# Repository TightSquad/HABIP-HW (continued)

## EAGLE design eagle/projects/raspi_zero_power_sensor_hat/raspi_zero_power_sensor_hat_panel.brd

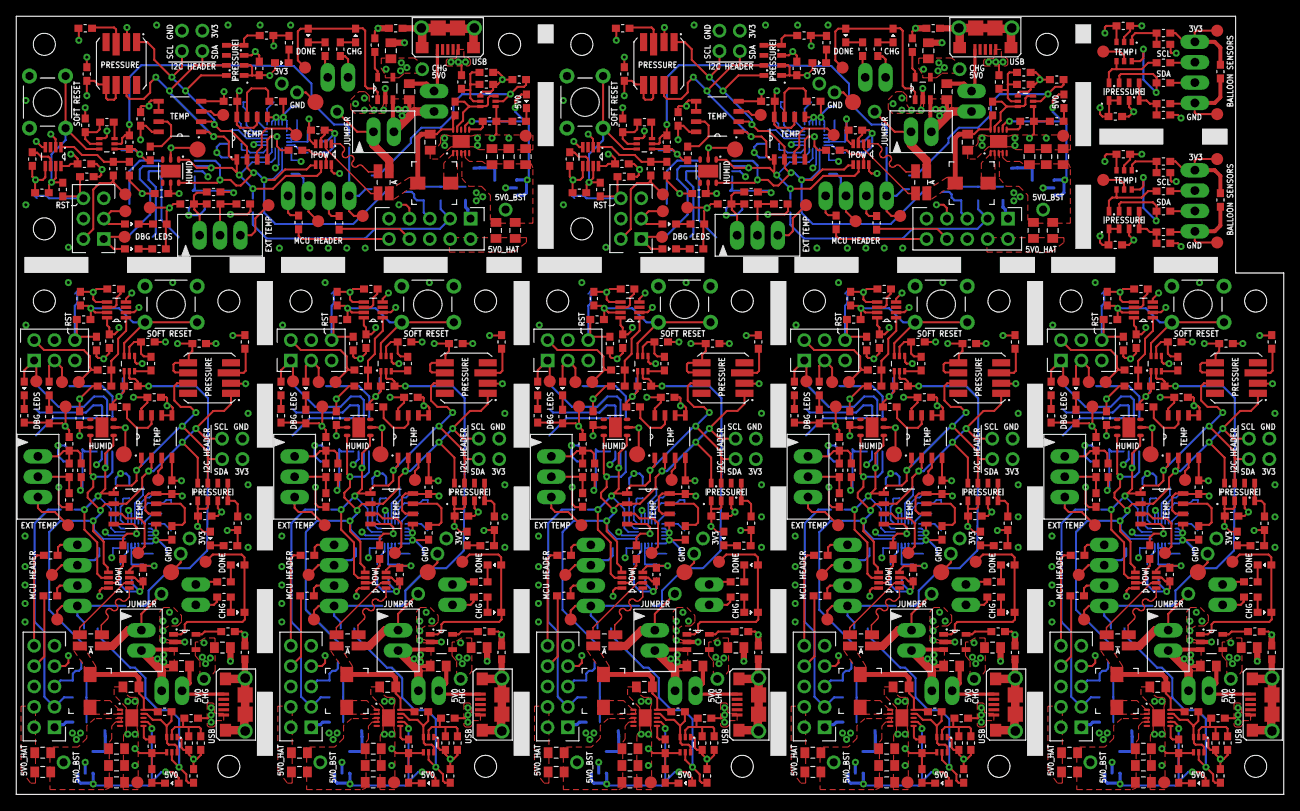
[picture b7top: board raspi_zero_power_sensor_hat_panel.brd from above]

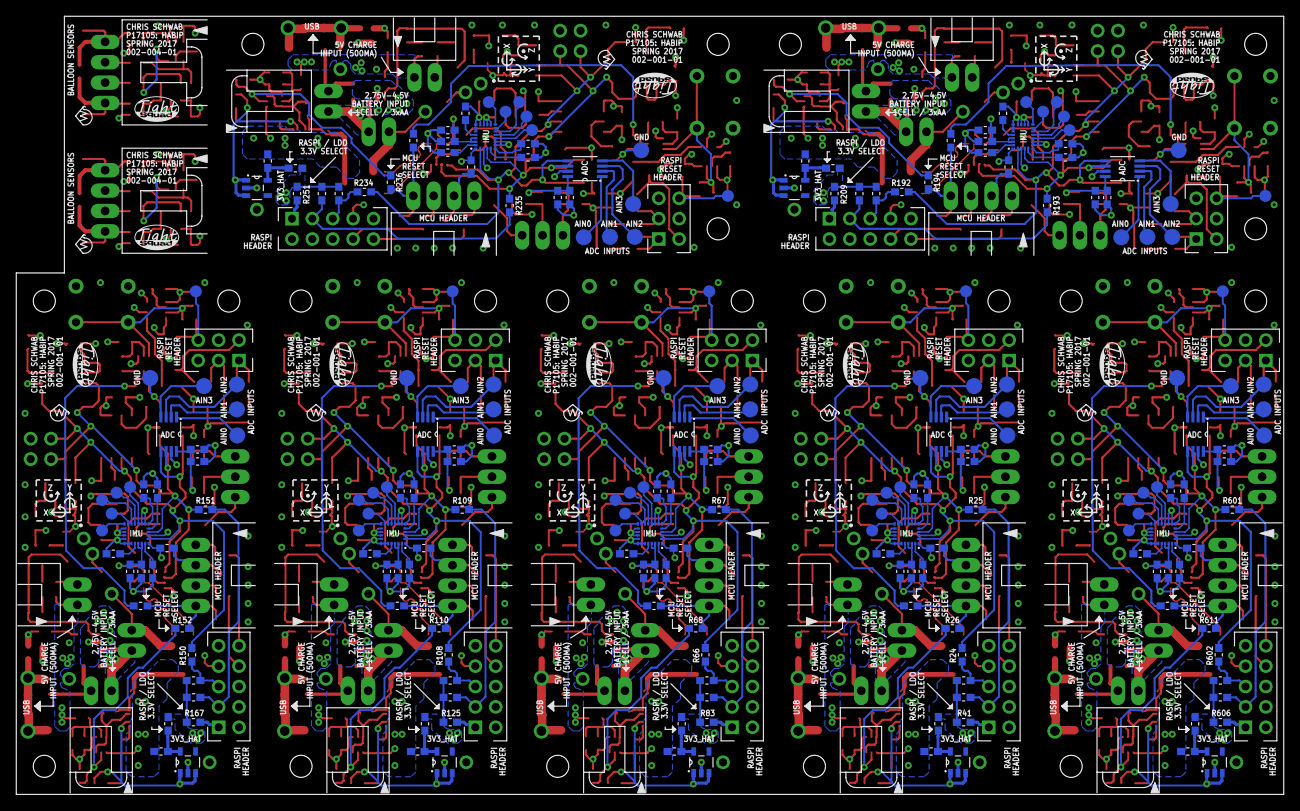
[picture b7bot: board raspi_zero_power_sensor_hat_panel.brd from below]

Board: 4 copper layers, 158.0 x 97.0 mm, 1126 parts (265 on the bottom side), 494 nets.

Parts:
BOM1, BOM4, BOM20, BOM23, BOM26, BOM42, BOM45, BOM48, BOM64, BOM67, BOM70, BOM86, BOM89, BOM92, BOM108, BOM111, BOM114, BOM130, BOM701, BOM704, BOM707: SL 70066 2PIN HOUSING; BLANK
BOM2, BOM3, BOM5, BOM6, BOM7, BOM8, BOM9, BOM10, BOM13, BOM14, BOM15, BOM21, BOM22, BOM24, BOM25, BOM27, BOM28, BOM29, BOM30, BOM31, BOM32, BOM35, BOM36, BOM37, BOM43, BOM44, BOM46, BOM47, BOM49, BOM50, BOM51, BOM52, BOM53, BOM54, BOM57, BOM58, BOM59, BOM65, BOM66, BOM68, BOM69, BOM71, BOM72, BOM73, BOM74, BOM75, BOM76, BOM79, BOM80, BOM81, BOM87, BOM88, BOM90, BOM91, BOM93, BOM94, BOM95, BOM96, BOM97, BOM98, BOM101, BOM102, BOM103, BOM109, BOM110, BOM112, BOM113, BOM115, BOM116, BOM117, BOM118, BOM119, BOM120, BOM123, BOM124, BOM125, BOM131, BOM132, BOM702, BOM703, BOM705, BOM706, BOM708, BOM709, BOM712, BOM713, BOM714, BOM715, BOM717, BOM718, BOM719: SL 70058 GOLD CRIMP; BLANK
BOM11, BOM33, BOM55, BOM77, BOM99, BOM121, BOM711: SL 70066 4PIN HOUSING; BLANK
BOM12, BOM34, BOM56, BOM78, BOM100, BOM122, BOM716: SL 70066 3PIN HOUSING; BLANK
BOM16, BOM17, BOM38, BOM39, BOM60, BOM61, BOM82, BOM83, BOM104, BOM105, BOM126, BOM127, BOM720, BOM721: 1-Wire Temperature Sensor; BLANK
BOM18, BOM40, BOM62, BOM84, BOM106, BOM128, BOM722: HEADER-RECT-MALE-2X3; BLANK
BOM19, BOM41, BOM63, BOM85, BOM107, BOM129, BOM710: HEADER-RECT-MALE-2X5; BLANK
C1, C2, C3, C4, C5, C6, C7, C8, C9, C10, C12, C14, C16, C17, C26, C27, C28, C29, C30, C31, C32, C33, C34, C35, C37, C39, C41, C42, C51, C52, C53, C54, C55, C56, C57, C58, C59, C60, C62, C64, C66, C67, C76, C77, C78, C79, C80, C81, C82, C83, C84, C85, C87, C89, C91, C92, C101, C102, C103, C104, C105, C106, C107, C108, C109, C110, C112, C114, C116, C117, C126, C127, C128, C129, C130, C131, C132, C133, C134, C135, C137, C139, C141, C142, C152, C153, C202, C203, C302, C402, C501, C502, C503, C506, C507, C508, C510, C511, C512, C513, C601, C602: 100nF; C0603
C11, C36, C61, C86, C111, C136, C509: 10uF; C0603
C13, C38, C63, C88, C113, C138, C505: 10nF; C0603
C15, C40, C65, C90, C115, C140, C404: 2.2uF; C0603
C18, C43, C68, C93, C118, C143, C504: 4.7uF; C0603
C19, C20, C22, C24, C25, C44, C45, C47, C49, C50, C69, C70, C72, C74, C75, C94, C95, C97, C99, C100, C119, C120, C122, C124, C125, C144, C145, C147, C149, C150, C301, C401, C406, C407, C408: 10uF; C0805
C21, C46, C71, C96, C121, C146, C405: 18nF; C0603
C23, C48, C73, C98, C123, C148, C403: 22uF; C0805
C151, C201: 1uF; C0603
DS1, DS7, DS13, DS19, DS25, DS31, DS401: BLUE; LED0603
DS2, DS8, DS14, DS20, DS26, DS32, DS302: GREEN; LED0603
DS3, DS4, DS5, DS6, DS9, DS10, DS11, DS12, DS15, DS16, DS17, DS18, DS21, DS22, DS23, DS24, DS27, DS28, DS29, DS30, DS33, DS34, DS35, DS36, DS301, DS402, DS601, DS602: YELLOW; LED0603
F1, F2, F3, F4, F5, F6, F601: FUSE-50MA; R0603
J1, J9, J17, J25, J33, J41, J401: MOL-SL-2-RA; MOLSL-2-RA
J2, J10, J18, J26, J34, J42, J603: MOL-SL-3-V; MOLSL-3-V
J3, J11, J19, J27, J35, J43, J604: RECEPTACLE-2x3-2.54MM; RECEPTACLE-2X3-254MM
J4, J12, J20, J28, J36, J44, J302: USB_MICROB_RECPT; MICROUSB-RIGHT
J5, J13, J21, J29, J37, J45, J301: MOL-SL-2-RA; MOLSL-2-RA_HALF
J6, J14, J22, J30, J38, J46, J601: RECEPTACLE-2x5-2.54MM; RECEPTACLE-2X5-254MM
J7, J15, J23, J31, J39, J47, J402: MOL-SL-2-V; MOLSL-2-V
J8, J16, J24, J32, J40, J48, J602: MOL-SL-4-RA; MOLSL-4-RA_HALF
J49, J201: MOL-SL-4-RA; MOLSL-4-RA
L1, L2, L3, L4, L5, L6, L401: 1.0uH; SMD410P190X160-2N
LOGO1, LOGO3, LOGO5, LOGO7, LOGO9, LOGO11, LOGO13, LOGO201, LOGO602: SQUAD_LOGO
LOGO2, LOGO4, LOGO6, LOGO8, LOGO10, LOGO12, LOGO14, LOGO202, LOGO601: CMS_LOGO
OUTLINE1, OUTLINE2, OUTLINE3, OUTLINE4, OUTLINE5, OUTLINE6, OUTLINE601: RASPI_ZERO_OUTLINE_3S0C_ONLY; RASPI_ZERO_3STANDOFFS_ONLY
Q1, Q2, Q3, Q4, Q5, Q6, Q7, Q8, Q9, Q10, Q11, Q12, Q301, Q401: SSM6N7002KFU; SOT363P080X040-6N
R1, R2, R3, R10, R11, R17, R19, R20, R23, R24, R25, R26, R27, R32, R33, R34, R35, R37, R38, R40, R41, R43, R44, R45, R52, R53, R59, R61, R62, R65, R66, R67, R68, R69, R74, R75, R76, R77, R79, R80, R82, R83, R85, R86, R87, R94, R95, R101, R103, R104, R107, R108, R109, R110, R111, R116, R117, R118, R119, R121, R122, R124, R125, R127, R128, R129, R136, R137, R143, R145, R146, R149, R150, R151, R152, R153, R158, R159, R160, R161, R163, R164, R166, R167, R169, R170, R171, R178, R179, R185, R187, R188, R191, R192, R193, R194, R195, R200, R201, R202, R203, R205, R206, R208, R209, R211, R212, R213, R220, R221, R227, R229, R230, R233, R234, R235, R236, R237, R242, R243, R244, R245, R247, R248, R250, R251, R253, R254, R255, R256, R257, R258, R259, R260, R261, R262, R263, R264, R301, R305, R306, R307, R308, R401, R501, R502, R503, R504, R505, R506, R507, R601, R602, R605, R606, R609, R610, R611, R612: 0.0; R0603
R4, R5, R6, R8, R9, R12, R13, R14, R18, R46, R47, R48, R50, R51, R54, R55, R56, R60, R88, R89, R90, R92, R93, R96, R97, R98, R102, R130, R131, R132, R134, R135, R138, R139, R140, R144, R172, R173, R174, R176, R177, R180, R181, R182, R186, R214, R215, R216, R218, R219, R222, R223, R224, R228, R302, R303, R304, R407, R410, R603, R604, R607, R608: 2k; R0603
R7, R49, R91, R133, R175, R217, R613: 4.7k; R0603
R15, R16, R28, R29, R30, R31, R57, R58, R70, R71, R72, R73, R99, R100, R112, R113, R114, R115, R141, R142, R154, R155, R156, R157, R183, R184, R196, R197, R198, R199, R225, R226, R238, R239, R240, R241, R309, R310, R311, R404, R405, R406: 10k; R0603
R21, R42, R63, R84, R105, R126, R147, R168, R189, R210, R231, R252, R408, R409: 0.0; R0805
R22, R36, R64, R78, R106, R120, R148, R162, R190, R204, R232, R246, R312, R403: 49.9; R0603
R39, R81, R123, R165, R207, R249, R402: 0.033; RS1206
S1, S2, S3, S4, S5, S6, S301: PB; TACTILE-PTH
TP1, TP2, TP3, TP4, TP5, TP6, TP7, TP8, TP9, TP10, TP11, TP12, TP13, TP21, TP24, TP26, TP27, TP34, TP35, TP36, TP37, TP38, TP39, TP40, TP41, TP42, TP43, TP44, TP45, TP46, TP54, TP57, TP59, TP60, TP67, TP68, TP69, TP70, TP71, TP72, TP73, TP74, TP75, TP76, TP77, TP78, TP79, TP87, TP90, TP92, TP93, TP100, TP101, TP102, TP103, TP104, TP105, TP106, TP107, TP108, TP109, TP110, TP111, TP112, TP120, TP123, TP125, TP126, TP133, TP134, TP135, TP136, TP137, TP138, TP139, TP140, TP141, TP142, TP143, TP144, TP145, TP153, TP156, TP158, TP159, TP166, TP167, TP168, TP169, TP170, TP171, TP172, TP173, TP174, TP175, TP176, TP177, TP178, TP186, TP189, TP191, TP192, TP199, TP200, TP201, TP202, TP203, TP204, TP304, TP404, TP506, TP507, TP508, TP509, TP510, TP511, TP512, TP605, TP606, TP607, TP608, TP609, TP610, TP611, TP612: TP15R
TP14, TP15, TP16, TP17, TP18, TP32, TP33, TP47, TP48, TP49, TP50, TP51, TP65, TP66, TP80, TP81, TP82, TP83, TP84, TP98, TP99, TP113, TP114, TP115, TP116, TP117, TP131, TP132, TP146, TP147, TP148, TP149, TP150, TP164, TP165, TP179, TP180, TP181, TP182, TP183, TP197, TP198, TP303, TP501, TP502, TP503, TP504, TP505, TP513: TP20R
TP19, TP20, TP22, TP23, TP25, TP28, TP29, TP30, TP31, TP52, TP53, TP55, TP56, TP58, TP61, TP62, TP63, TP64, TP85, TP86, TP88, TP89, TP91, TP94, TP95, TP96, TP97, TP118, TP119, TP121, TP122, TP124, TP127, TP128, TP129, TP130, TP151, TP152, TP154, TP155, TP157, TP160, TP161, TP162, TP163, TP184, TP185, TP187, TP188, TP190, TP193, TP194, TP195, TP196, TP301, TP302, TP401, TP402, TP403, TP601, TP602, TP603, TP604: TP_TH102
U1, U13, U25, U37, U49, U61, U504: INA219AIDCNR; SOT65P110X045-8N
U2, U14, U26, U38, U50, U62, U73, U202, U506: MS560702BA03-50; SMD125P110X060-8N
U3, U15, U27, U39, U51, U63, U503: MAX11613EUA+; SOP65P135X040-8N
U4, U16, U28, U40, U52, U64, U507: MS580305BA01; SMD125130P225X090-8N
U5, U17, U29, U41, U53, U65, U401: TLV71333P; SOT23P105X060-5N
U6, U18, U30, U42, U54, U66, U302: MAX6371; SOT23P130X045-8N
U7, U19, U31, U43, U55, U67, U505: LSM9DS1TR; LGA043P045X033-24N
U8, U20, U32, U44, U56, U68, U508: SI7021; DFN-100P085X045-T-6N
U9, U21, U33, U45, U57, U69, U301: MCP73831T-2AC; SOT23P110X060-5N
U10, U22, U34, U46, U58, U70, U402: TPS61232; DRC0010G_SM
U11, U12, U23, U24, U35, U36, U47, U48, U59, U60, U71, U72, U501, U502: PCT2075D,118; SOIC127P130X0600-8N
U74, U201: PCT2075GVJ; TSOP95P080X055-6N

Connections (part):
3V3_HAT_PG: DS402.1, R410.2
3V3_HAT_PG1: DS4.1, R18.2
3V3_HAT_PG2: DS10.1, R60.2
3V3_HAT_PG3: DS16.1, R102.2
3V3_HAT_PG4: DS22.1, R144.2
3V3_HAT_PG5: DS28.1, R186.2
3V3_HAT_PG6: DS34.1, R228.2
5V0_BST_PG: DS401.1, R407.2
5V0_BST_PG1: DS1.1, R4.2
5V0_BST_PG2: DS7.1, R46.2
5V0_BST_PG3: DS13.1, R88.2
5V0_BST_PG4: DS19.1, R130.2
5V0_BST_PG5: DS25.1, R172.2
5V0_BST_PG6: DS31.1, R214.2
ADC_AIN0: TP504.TP, U503.1
ADC_AIN1: TP503.TP, U503.2
ADC_AIN2: TP502.TP, U503.3
ADC_AIN3: TP15.TP, U3.3
ADC_AIN3_REF: TP501.TP, U503.4
ADC_AIN3_REF1: TP14.TP, U3.4
ADC_AIN3_REF2: TP47.TP, U15.4
ADC_AIN3_REF3: TP80.TP, U27.4
ADC_AIN3_REF4: TP113.TP, U39.4
ADC_AIN3_REF5: TP146.TP, U51.4
ADC_AIN3_REF6: TP179.TP, U63.4
ADC_AIN4: TP16.TP, U3.2
ADC_AIN5: TP17.TP, U3.1
ADC_AIN6: TP48.TP, U15.3
ADC_AIN7: TP49.TP, U15.2
ADC_AIN8: TP50.TP, U15.1
ADC_AIN9: TP81.TP, U27.3
ADC_AIN10: TP82.TP, U27.2
ADC_AIN11: TP83.TP, U27.1
ADC_AIN12: TP114.TP, U39.3
ADC_AIN13: TP115.TP, U39.2
ADC_AIN14: TP116.TP, U39.1
ADC_AIN15: TP147.TP, U51.3
ADC_AIN16: TP148.TP, U51.2
ADC_AIN17: TP149.TP, U51.1
ADC_AIN18: TP180.TP, U63.3
ADC_AIN19: TP181.TP, U63.2
ADC_AIN20: TP182.TP, U63.1
BST_EN: Q401.3, Q401.6, R405.1, U402.9
BST_EN1: Q1.3, Q1.6, R29.1, U10.9
BST_EN2: Q3.3, Q3.6, R71.1, U22.9
BST_EN3: Q5.3, Q5.6, R113.1, U34.9
BST_EN4: Q7.3, Q7.6, R155.1, U46.9
BST_EN5: Q9.3, Q9.6, R197.1, U58.9
BST_EN6: Q11.3, Q11.6, R239.1, U70.9
BST_SS: C405.1, U402.6
BST_SS1: C21.1, U10.6
BST_SS2: C46.1, U22.6
BST_SS3: C71.1, U34.6
BST_SS4: C96.1, U46.6
BST_SS5: C121.1, U58.6
BST_SS6: C146.1, U70.6
BST_SW: L401.2, U402.1, U402.2
BST_SW1: L1.2, U10.1, U10.2
BST_SW2: L2.2, U22.1, U22.2
BST_SW3: L3.2, U34.1, U34.2
BST_SW4: L4.2, U46.1, U46.2
BST_SW5: L5.2, U58.1, U58.2
BST_SW6: L6.2, U70.1, U70.2
CHG_DISABLE_GATE: C404.1, Q401.2, R403.2, R404.2
CHG_DISABLE_GATE1: C15.1, Q1.2, R30.2, R36.2
CHG_DISABLE_GATE2: C40.1, Q3.2, R72.2, R78.2
CHG_DISABLE_GATE3: C65.1, Q5.2, R114.2, R120.2
CHG_DISABLE_GATE4: C90.1, Q7.2, R156.2, R162.2
CHG_DISABLE_GATE5: C115.1, Q9.2, R198.2, R204.2
CHG_DISABLE_GATE6: C140.1, Q11.2, R240.2, R246.2
CHG_DONE: DS302.1, R304.2
CHG_DONE1: DS2.1, R14.2
CHG_DONE2: DS8.1, R56.2
CHG_DONE3: DS14.1, R98.2
CHG_DONE4: DS20.1, R140.2
CHG_DONE5: DS26.1, R182.2
CHG_DONE6: DS32.1, R224.2
CHG_ON: DS301.2, R303.1
CHG_ON1: DS3.2, R13.1
CHG_ON2: DS9.2, R55.1
CHG_ON3: DS15.2, R97.1
CHG_ON4: DS21.2, R139.1
CHG_ON5: DS27.2, R181.1
CHG_ON6: DS33.2, R223.1
CHG_PROG: R302.2, U301.5
CHG_PROG1: R12.2, U9.5
CHG_PROG2: R54.2, U21.5
CHG_PROG3: R96.2, U33.5
CHG_PROG4: R138.2, U45.5
CHG_PROG5: R180.2, U57.5
CHG_PROG6: R222.2, U69.5
CHG_STAT: DS301.1, DS302.2, TP304.TP, U301.1
CHG_STAT1: DS2.2, DS3.1, TP21.TP, U9.1
CHG_STAT2: DS8.2, DS9.1, TP54.TP, U21.1
CHG_STAT3: DS14.2, DS15.1, TP87.TP, U33.1
CHG_STAT4: DS20.2, DS21.1, TP120.TP, U45.1
CHG_STAT5: DS26.2, DS27.1, TP153.TP, U57.1
CHG_STAT6: DS32.2, DS33.1, TP186.TP, U69.1
DBG_LED0: DS601.1, R607.2
DBG_LED1: DS602.1, R608.2
DBG_LED2: DS6.1, R9.2
DBG_LED3: DS5.1, R8.2
DBG_LED4: DS12.1, R51.2
DBG_LED5: DS11.1, R50.2
DBG_LED6: DS18.1, R93.2
DBG_LED7: DS17.1, R92.2
DBG_LED8: DS24.1, R135.2
DBG_LED9: DS23.1, R134.2
DBG_LED10: DS30.1, R177.2
DBG_LED11: DS29.1, R176.2
DBG_LED12: DS36.1, R219.2
DBG_LED13: DS35.1, R218.2
FET_D: Q301.3, R305.2
FET_D1: Q2.3, R37.2
FET_D2: Q4.3, R79.2
FET_D3: Q6.3, R121.2
FET_D4: Q8.3, R163.2
FET_D5: Q10.3, R205.2
FET_D6: Q12.3, R247.2
FET_G: Q301.5, R305.1, R306.1
FET_G1: Q2.5, R37.1, R38.1
FET_G2: Q4.5, R79.1, R80.1
FET_G3: Q6.5, R121.1, R122.1
FET_G4: Q8.5, R163.1, R164.1
FET_G5: Q10.5, R205.1, R206.1
FET_G6: Q12.5, R247.1, R248.1
GND: C301.2, C302.2, C401.2, C402.2, C403.2, C404.2, C405.2, C406.2, C407.2, C408.2, C501.1, C502.1, C503.2, C504.2, C505.2, C506.1, C507.2, C508.2, C509.2, C510.2, C511.1, C512.1, C513.1, C601.2, C602.2, J301.2, J302.5, J401.2, J601.6, J601.9, J602.2, J603.3, J604.4, J604.5, Q301.1, Q301.4, Q401.1, Q401.4, R301.1, R302.1, R304.1, R306.2, R309.1, R310.1, R404.1, R406.1, R407.1, R410.1, R501.1, R502.1, R503.1, R504.1, R505.1, R507.1, R607.1, R608.1, S301.1, S301.2, TP302.1, TP303.TP, TP404.TP, TP505.TP, TP513.TP, TP604.1, TP608.TP, TP610.TP, TP612.TP, U301.2, U302.2, U401.2, U402.11, U501.4, U501.5, U501.6, U502.4, U502.5, U503.7, U504.3, U505.14, U505.15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
GND1: C1.1, C2.1, C3.1, C4.1, C5.2, C6.2, C7.1, C8.1, C9.2, C10.2, C11.2, C12.2, C13.2, C14.2, C15.2, C16.2, C17.2, C18.2, C19.2, C20.2, C21.2, C22.2, C23.2, C24.2, C25.2, J1.2, J2.3, J3.4, J3.5, J4.5, J5.2, J6.6, J6.9, J8.2, Q1.1, Q1.4, Q2.1, Q2.4, R1.1, R2.1, R3.1, R4.1, R8.1, R9.1, R10.1, R12.1, R14.1, R16.1, R18.1, R19.1, R20.1, R23.1, R28.1, R30.1, R31.1, R38.2, S1.1, S1.2, TP11.TP, TP12.TP, TP13.TP, TP18.TP, TP20.1, TP24.TP, TP31.1, TP32.TP, TP33.TP, U1.3, U2.3, U3.7, U4.2, U5.2, U6.2, U7.14, U7.15, U7.16, U7.17, U7.18, U7.19, U7.20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
GND2: C26.1, C27.1, C28.1, C29.1, C30.2, C31.2, C32.1, C33.1, C34.2, C35.2, C36.2, C37.2, C38.2, C39.2, C40.2, C41.2, C42.2, C43.2, C44.2, C45.2, C46.2, C47.2, C48.2, C49.2, C50.2, J9.2, J10.3, J11.4, J11.5, J12.5, J13.2, J14.6, J14.9, J16.2, Q3.1, Q3.4, Q4.1, Q4.4, R43.1, R44.1, R45.1, R46.1, R50.1, R51.1, R52.1, R54.1, R56.1, R58.1, R60.1, R61.1, R62.1, R65.1, R70.1, R72.1, R73.1, R80.2, S2.1, S2.2, TP44.TP, TP45.TP, TP46.TP, TP51.TP, TP53.1, TP57.TP, TP64.1, TP65.TP, TP66.TP, U13.3, U14.3, U15.7, U16.2, U17.2, U18.2, U19.14, U19.15, U19.16, U19.17, U19.18, U19.19, U19.20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
GND3: C51.1, C52.1, C53.1, C54.1, C55.2, C56.2, C57.1, C58.1, C59.2, C60.2, C61.2, C62.2, C63.2, C64.2, C65.2, C66.2, C67.2, C68.2, C69.2, C70.2, C71.2, C72.2, C73.2, C74.2, C75.2, J17.2, J18.3, J19.4, J19.5, J20.5, J21.2, J22.6, J22.9, J24.2, Q5.1, Q5.4, Q6.1, Q6.4, R85.1, R86.1, R87.1, R88.1, R92.1, R93.1, R94.1, R96.1, R98.1, R100.1, R102.1, R103.1, R104.1, R107.1, R112.1, R114.1, R115.1, R122.2, S3.1, S3.2, TP77.TP, TP78.TP, TP79.TP, TP84.TP, TP86.1, TP90.TP, TP97.1, TP98.TP, TP99.TP, U25.3, U26.3, U27.7, U28.2, U29.2, U30.2, U31.14, U31.15, U31.16, U31.17, U31.18, U31.19, U31.20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
GND4: C76.1, C77.1, C78.1, C79.1, C80.2, C81.2, C82.1, C83.1, C84.2, C85.2, C86.2, C87.2, C88.2, C89.2, C90.2, C91.2, C92.2, C93.2, C94.2, C95.2, C96.2, C97.2, C98.2, C99.2, C100.2, J25.2, J26.3, J27.4, J27.5, J28.5, J29.2, J30.6, J30.9, J32.2, Q7.1, Q7.4, Q8.1, Q8.4, R127.1, R128.1, R129.1, R130.1, R134.1, R135.1, R136.1, R138.1, R140.1, R142.1, R144.1, R145.1, R146.1, R149.1, R154.1, R156.1, R157.1, R164.2, S4.1, S4.2, TP110.TP, TP111.TP, TP112.TP, TP117.TP, TP119.1, TP123.TP, TP130.1, TP131.TP, TP132.TP, U37.3, U38.3, U39.7, U40.2, U41.2, U42.2, U43.14, U43.15, U43.16, U43.17, U43.18, U43.19, U43.20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
GND5: C101.1, C102.1, C103.1, C104.1, C105.2, C106.2, C107.1, C108.1, C109.2, C110.2, C111.2, C112.2, C113.2, C114.2, C115.2, C116.2, C117.2, C118.2, C119.2, C120.2, C121.2, C122.2, C123.2, C124.2, C125.2, J33.2, J34.3, J35.4, J35.5, J36.5, J37.2, J38.6, J38.9, J40.2, Q9.1, Q9.4, Q10.1, Q10.4, R169.1, R170.1, R171.1, R172.1, R176.1, R177.1, R178.1, R180.1, R182.1, R184.1, R186.1, R187.1, R188.1, R191.1, R196.1, R198.1, R199.1, R206.2, S5.1, S5.2, TP143.TP, TP144.TP, TP145.TP, TP150.TP, TP152.1, TP156.TP, TP163.1, TP164.TP, TP165.TP, U49.3, U50.3, U51.7, U52.2, U53.2, U54.2, U55.14, U55.15, U55.16, U55.17, U55.18, U55.19, U55.20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
GND6: C126.1, C127.1, C128.1, C129.1, C130.2, C131.2, C132.1, C133.1, C134.2, C135.2, C136.2, C137.2, C138.2, C139.2, C140.2, C141.2, C142.2, C143.2, C144.2, C145.2, C146.2, C147.2, C148.2, C149.2, C150.2, J41.2, J42.3, J43.4, J43.5, J44.5, J45.2, J46.6, J46.9, J48.2, Q11.1, Q11.4, Q12.1, Q12.4, R211.1, R212.1, R213.1, R214.1, R218.1, R219.1, R220.1, R222.1, R224.1, R226.1, R228.1, R229.1, R230.1, R233.1, R238.1, R240.1, R241.1, R248.2, S6.1, S6.2, TP176.TP, TP177.TP, TP178.TP, TP183.TP, TP185.1, TP189.TP, TP196.1, TP197.TP, TP198.TP, U61.3, U62.3, U63.7, U64.2, U65.2, U66.2, U67.14, U67.15, U67.16, U67.17, U67.18, U67.19, U67.20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
GND7: C201.2, C202.1, C203.1, J201.4, R255.1, R256.1, TP202.TP, U201.2, U202.3
GND8: C151.2, C152.1, C153.1, J49.4, R261.1, R262.1, TP200.TP, U73.3, U74.2
I2C1_RASPI_SCL: R602.1, TP603.1, U501.2, U502.2, U503.5, U504.5, U505.2, U506.8, U507.1, U508.6
I2C1_RASPI_SCL1: R24.1, TP30.1, U1.5, U2.8, U3.5, U4.1, U7.2, U8.6, U11.2, U12.2
I2C1_RASPI_SCL2: R66.1, TP63.1, U13.5, U14.8, U15.5, U16.1, U19.2, U20.6, U23.2, U24.2
I2C1_RASPI_SCL3: R108.1, TP96.1, U25.5, U26.8, U27.5, U28.1, U31.2, U32.6, U35.2, U36.2
I2C1_RASPI_SCL4: R150.1, TP129.1, U37.5, U38.8, U39.5, U40.1, U43.2, U44.6, U47.2, U48.2
I2C1_RASPI_SCL5: R192.1, TP162.1, U49.5, U50.8, U51.5, U52.1, U55.2, U56.6, U59.2, U60.2
I2C1_RASPI_SCL6: R234.1, TP195.1, U61.5, U62.8, U63.5, U64.1, U67.2, U68.6, U71.2, U72.2
I2C1_RASPI_SCL_R: J601.5, R602.2, R604.1
I2C1_RASPI_SCL_R1: J6.5, R6.1, R24.2
I2C1_RASPI_SCL_R2: J14.5, R48.1, R66.2
I2C1_RASPI_SCL_R3: J22.5, R90.1, R108.2
I2C1_RASPI_SCL_R4: J30.5, R132.1, R150.2
I2C1_RASPI_SCL_R5: J38.5, R174.1, R192.2
I2C1_RASPI_SCL_R6: J46.5, R216.1, R234.2
I2C1_RASPI_SDA: R601.1, TP602.1, U501.1, U502.1, U503.6, U504.6, U505.4, U506.7, U507.7, U508.1
I2C1_RASPI_SDA1: R25.1, TP29.1, U1.6, U2.7, U3.6, U4.7, U7.4, U8.1, U11.1, U12.1
I2C1_RASPI_SDA2: R67.1, TP62.1, U13.6, U14.7, U15.6, U16.7, U19.4, U20.1, U23.1, U24.1
I2C1_RASPI_SDA3: R109.1, TP95.1, U25.6, U26.7, U27.6, U28.7, U31.4, U32.1, U35.1, U36.1
I2C1_RASPI_SDA4: R151.1, TP128.1, U37.6, U38.7, U39.6, U40.7, U43.4, U44.1, U47.1, U48.1
I2C1_RASPI_SDA5: R193.1, TP161.1, U49.6, U50.7, U51.6, U52.7, U55.4, U56.1, U59.1, U60.1
I2C1_RASPI_SDA6: R235.1, TP194.1, U61.6, U62.7, U63.6, U64.7, U67.4, U68.1, U71.1, U72.1
I2C1_RASPI_SDA_R: J601.3, R601.2, R603.1
I2C1_RASPI_SDA_R1: J6.3, R5.1, R25.2
I2C1_RASPI_SDA_R2: J14.3, R47.1, R67.2
I2C1_RASPI_SDA_R3: J22.3, R89.1, R109.2
I2C1_RASPI_SDA_R4: J30.3, R131.1, R151.2
I2C1_RASPI_SDA_R5: J38.3, R173.1, R193.2
I2C1_RASPI_SDA_R6: J46.3, R215.1, R235.2
I2C_SCL: R253.2, U201.4, U202.8
I2C_SCL1: R259.2, U73.8, U74.4
I2C_SCL_CONN: J201.2, R253.1
I2C_SCL_CONN1: J49.2, R259.1
I2C_SDA: R254.2, U201.6, U202.7
I2C_SDA1: R260.2, U73.7, U74.6
I2C_SDA_COMM: J201.3, R254.1
I2C_SDA_COMM1: J49.3, R260.1
IMON_A0: R504.2, U504.7
IMON_A1: R3.2, U1.7
IMON_A2: R45.2, U13.7
IMON_A3: R87.2, U25.7
IMON_A4: R129.2, U37.7
IMON_A5: R171.2, U49.7
IMON_A6: R213.2, U61.7
IMU_C1: C508.1, U505.24
IMU_C2: C12.1, U7.24
IMU_C3: C37.1, U19.24
IMU_C4: C62.1, U31.24
IMU_C5: C87.1, U43.24
IMU_C6: C112.1, U55.24
IMU_C7: C137.1, U67.24
IMU_CAP: C505.1, U505.21
IMU_CAP1: C13.1, U7.21
IMU_CAP2: C38.1, U19.21
IMU_CAP3: C63.1, U31.21
IMU_CAP4: C88.1, U43.21
IMU_CAP5: C113.1, U55.21
IMU_CAP6: C138.1, U67.21
IMU_DEN_AG: TP512.TP, U505.13
IMU_DEN_AG1: TP10.TP, U7.13
IMU_DEN_AG2: TP43.TP, U19.13
IMU_DEN_AG3: TP76.TP, U31.13
IMU_DEN_AG4: TP109.TP, U43.13
IMU_DEN_AG5: TP142.TP, U55.13
IMU_DEN_AG6: TP175.TP, U67.13
IMU_DRDY_M: TP508.TP, U505.9
IMU_DRDY_M1: TP6.TP, U7.9
IMU_DRDY_M2: TP39.TP, U19.9
IMU_DRDY_M3: TP72.TP, U31.9
IMU_DRDY_M4: TP105.TP, U43.9
IMU_DRDY_M5: TP138.TP, U55.9
IMU_DRDY_M6: TP171.TP, U67.9
IMU_INT1_AG: TP510.TP, U505.11
IMU_INT1_AG1: TP8.TP, U7.11
IMU_INT1_AG2: TP41.TP, U19.11
IMU_INT1_AG3: TP74.TP, U31.11
IMU_INT1_AG4: TP107.TP, U43.11
IMU_INT1_AG5: TP140.TP, U55.11
IMU_INT1_AG6: TP173.TP, U67.11
IMU_INT2_AG: TP511.TP, U505.12
IMU_INT2_AG1: TP9.TP, U7.12
IMU_INT2_AG2: TP42.TP, U19.12
IMU_INT2_AG3: TP75.TP, U31.12
IMU_INT2_AG4: TP108.TP, U43.12
IMU_INT2_AG5: TP141.TP, U55.12
IMU_INT2_AG6: TP174.TP, U67.12
IMU_INT_M: TP509.TP, U505.10
IMU_INT_M1: TP7.TP, U7.10
IMU_INT_M2: TP40.TP, U19.10
IMU_INT_M3: TP73.TP, U31.10
IMU_INT_M4: TP106.TP, U43.10
IMU_INT_M5: TP139.TP, U55.10
IMU_INT_M6: TP172.TP, U67.10
IMU_SDO_AG: R505.2, U505.5
IMU_SDO_AG1: R19.2, U7.5
IMU_SDO_AG2: R61.2, U19.5
IMU_SDO_AG3: R103.2, U31.5
IMU_SDO_AG4: R145.2, U43.5
IMU_SDO_AG5: R187.2, U55.5
IMU_SDO_AG6: R229.2, U67.5
IMU_SDO_M: R503.2, U505.6
IMU_SDO_M1: R20.2, U7.6
IMU_SDO_M2: R62.2, U19.6
IMU_SDO_M3: R104.2, U31.6
IMU_SDO_M4: R146.2, U43.6
IMU_SDO_M5: R188.2, U55.6
IMU_SDO_M6: R230.2, U67.6
MCU_TO_BST_RESET: Q401.5, R406.2, R611.2
MCU_TO_BST_RESET1: Q1.5, R26.2, R31.2
MCU_TO_BST_RESET2: Q3.5, R68.2, R73.2
MCU_TO_BST_RESET3: Q5.5, R110.2, R115.2
MCU_TO_BST_RESET4: Q7.5, R152.2, R157.2
MCU_TO_BST_RESET5: Q9.5, R194.2, R199.2
MCU_TO_BST_RESET6: Q11.5, R236.2, R241.2
MCU_TO_HAT_RESET: J602.4, R611.1, R612.1, TP607.TP
MCU_TO_HAT_RESET1: J8.4, R26.1, R27.1, TP5.TP
MCU_TO_HAT_RESET2: J16.4, R68.1, R69.1, TP38.TP
MCU_TO_HAT_RESET3: J24.4, R110.1, R111.1, TP71.TP
MCU_TO_HAT_RESET4: J32.4, R152.1, R153.1, TP104.TP
MCU_TO_HAT_RESET5: J40.4, R194.1, R195.1, TP137.TP
MCU_TO_HAT_RESET6: J48.4, R236.1, R237.1, TP170.TP
MCU_TO_RASPI_RESET: Q301.2, R310.2, R612.2
MCU_TO_RASPI_RESET1: Q2.2, R27.2, R28.2
MCU_TO_RASPI_RESET2: Q4.2, R69.2, R70.2
MCU_TO_RASPI_RESET3: Q6.2, R111.2, R112.2
MCU_TO_RASPI_RESET4: Q8.2, R153.2, R154.2
MCU_TO_RASPI_RESET5: Q10.2, R195.2, R196.2
MCU_TO_RASPI_RESET6: Q12.2, R237.2, R238.2
PP3V1: C151.1, C152.2, C153.2, J49.1, R263.2, R264.2, TP204.TP, U73.1, U73.2, U74.3
PP3V3: C201.1, C202.2, C203.2, J201.1, R257.2, R258.2, TP201.TP, U201.3, U202.1, U202.2
PP3V3_HAT: C302.1, C501.2, C502.2, C503.1, C504.1, C506.2, C507.1, C509.1, C510.1, C511.2, C512.2, C513.2, DS402.2, F601.2, R308.2, R311.2, R401.2, R506.2, R603.2, R604.2, R606.1, TP402.1, TP601.1, U302.4, U302.5, U302.8, U501.8, U502.6, U502.8, U503.8, U504.4, U504.8, U505.1, U505.3, U505.7, U505.8, U505.22, U505.23, U506.1, U506.2, U507.5, U507.6, U508.5
PP3V3_HAT1: C1.2, C2.2, C3.2, C4.2, C6.1, C7.2, C8.2, C9.1, C10.1, C11.1, C17.1, C18.1, DS4.2, F1.2, R5.2, R6.2, R11.2, R15.2, R17.2, R40.2, R41.1, TP25.1, TP28.1, U1.4, U1.8, U2.1, U2.2, U3.8, U4.5, U4.6, U6.4, U6.5, U6.8, U7.1, U7.3, U7.7, U7.8, U7.22, U7.23, U8.5, U11.8, U12.6, U12.8
PP3V3_HAT2: C26.2, C27.2, C28.2, C29.2, C31.1, C32.2, C33.2, C34.1, C35.1, C36.1, C42.1, C43.1, DS10.2, F2.2, R47.2, R48.2, R53.2, R57.2, R59.2, R82.2, R83.1, TP58.1, TP61.1, U13.4, U13.8, U14.1, U14.2, U15.8, U16.5, U16.6, U18.4, U18.5, U18.8, U19.1, U19.3, U19.7, U19.8, U19.22, U19.23, U20.5, U23.8, U24.6, U24.8
PP3V3_HAT3: C51.2, C52.2, C53.2, C54.2, C56.1, C57.2, C58.2, C59.1, C60.1, C61.1, C67.1, C68.1, DS16.2, F3.2, R89.2, R90.2, R95.2, R99.2, R101.2, R124.2, R125.1, TP91.1, TP94.1, U25.4, U25.8, U26.1, U26.2, U27.8, U28.5, U28.6, U30.4, U30.5, U30.8, U31.1, U31.3, U31.7, U31.8, U31.22, U31.23, U32.5, U35.8, U36.6, U36.8
PP3V3_HAT4: C76.2, C77.2, C78.2, C79.2, C81.1, C82.2, C83.2, C84.1, C85.1, C86.1, C92.1, C93.1, DS22.2, F4.2, R131.2, R132.2, R137.2, R141.2, R143.2, R166.2, R167.1, TP124.1, TP127.1, U37.4, U37.8, U38.1, U38.2, U39.8, U40.5, U40.6, U42.4, U42.5, U42.8, U43.1, U43.3, U43.7, U43.8, U43.22, U43.23, U44.5, U47.8, U48.6, U48.8
PP3V3_HAT5: C101.2, C102.2, C103.2, C104.2, C106.1, C107.2, C108.2, C109.1, C110.1, C111.1, C117.1, C118.1, DS28.2, F5.2, R173.2, R174.2, R179.2, R183.2, R185.2, R208.2, R209.1, TP157.1, TP160.1, U49.4, U49.8, U50.1, U50.2, U51.8, U52.5, U52.6, U54.4, U54.5, U54.8, U55.1, U55.3, U55.7, U55.8, U55.22, U55.23, U56.5, U59.8, U60.6, U60.8
PP3V3_HAT6: C126.2, C127.2, C128.2, C129.2, C131.1, C132.2, C133.2, C134.1, C135.1, C136.1, C142.1, C143.1, DS34.2, F6.2, R215.2, R216.2, R221.2, R225.2, R227.2, R250.2, R251.1, TP190.1, TP193.1, U61.4, U61.8, U62.1, U62.2, U63.8, U64.5, U64.6, U66.4, U66.5, U66.8, U67.1, U67.3, U67.7, U67.8, U67.22, U67.23, U68.5, U71.8, U72.6, U72.8
PP3V3_LDO: C402.1, R401.1, U401.5
PP3V3_LDO1: C5.1, R40.1, U5.5
PP3V3_LDO2: C30.1, R82.1, U17.5
PP3V3_LDO3: C55.1, R124.1, U29.5
PP3V3_LDO4: C80.1, R166.1, U41.5
PP3V3_LDO5: C105.1, R208.1, U53.5
PP3V3_LDO6: C130.1, R250.1, U65.5
PP3V3_RASPI: J601.1, R606.2
PP3V3_RASPI1: J6.1, R41.2
PP3V3_RASPI2: J14.1, R83.2
PP3V3_RASPI3: J22.1, R125.2
PP3V3_RASPI4: J30.1, R167.2
PP3V3_RASPI5: J38.1, R209.2
PP3V3_RASPI6: J46.1, R251.2
PP3V3_TEMP: C602.1, F601.1, J603.1, R613.2
PP3V3_TEMP1: C16.1, F1.1, J2.1, R7.2
PP3V3_TEMP2: C41.1, F2.1, J10.1, R49.2
PP3V3_TEMP3: C66.1, F3.1, J18.1, R91.2
PP3V3_TEMP4: C91.1, F4.1, J26.1, R133.2
PP3V3_TEMP5: C116.1, F5.1, J34.1, R175.2
PP3V3_TEMP6: C141.1, F6.1, J42.1, R217.2
PP5V0_BST: C406.1, C407.1, C408.1, DS401.2, R408.1, R409.1, TP403.1, U401.1, U401.3, U402.3, U402.4, U402.7
PP5V0_BST1: C22.1, C24.1, C25.1, DS1.2, R21.1, R42.1, TP23.1, U5.1, U5.3, U10.3, U10.4, U10.7
PP5V0_BST2: C47.1, C49.1, C50.1, DS7.2, R63.1, R84.1, TP56.1, U17.1, U17.3, U22.3, U22.4, U22.7
PP5V0_BST3: C72.1, C74.1, C75.1, DS13.2, R105.1, R126.1, TP89.1, U29.1, U29.3, U34.3, U34.4, U34.7
PP5V0_BST4: C97.1, C99.1, C100.1, DS19.2, R147.1, R168.1, TP122.1, U41.1, U41.3, U46.3, U46.4, U46.7
PP5V0_BST5: C122.1, C124.1, C125.1, DS25.2, R189.1, R210.1, TP155.1, U53.1, U53.3, U58.3, U58.4, U58.7
PP5V0_BST6: C147.1, C149.1, C150.1, DS31.2, R231.1, R252.1, TP188.1, U65.1, U65.3, U70.3, U70.4, U70.7
PP5V0_BST_HAT: J601.2, J601.4, R408.2, R409.2
PP5V0_BST_HAT1: J6.2, J6.4, R21.2, R42.2
PP5V0_BST_HAT2: J14.2, J14.4, R63.2, R84.2
PP5V0_BST_HAT3: J22.2, J22.4, R105.2, R126.2
PP5V0_BST_HAT4: J30.2, J30.4, R147.2, R168.2
PP5V0_BST_HAT5: J38.2, J38.4, R189.2, R210.2
PP5V0_BST_HAT6: J46.2, J46.4, R231.2, R252.2
PP5V0_CHG_IN: C301.1, J301.1, J302.1, R303.2, R403.1, TP301.1, U301.4
PP5V0_CHG_IN1: C19.1, J4.1, J5.1, R13.2, R36.1, TP19.1, U9.4
PP5V0_CHG_IN2: C44.1, J12.1, J13.1, R55.2, R78.1, TP52.1, U21.4
PP5V0_CHG_IN3: C69.1, J20.1, J21.1, R97.2, R120.1, TP85.1, U33.4
PP5V0_CHG_IN4: C94.1, J28.1, J29.1, R139.2, R162.1, TP118.1, U45.4
PP5V0_CHG_IN5: C119.1, J36.1, J37.1, R181.2, R204.1, TP151.1, U57.4
PP5V0_CHG_IN6: C144.1, J44.1, J45.1, R223.2, R246.1, TP184.1, U69.4
PRES0_CSB: R507.2, U506.4, U506.5
PRES0_CSB1: R1.2, U2.4, U2.5
PRES0_CSB2: R43.2, U14.4, U14.5
PRES0_CSB3: R85.2, U26.4, U26.5
PRES0_CSB4: R127.2, U38.4, U38.5
PRES0_CSB5: R169.2, U50.4, U50.5
PRES0_CSB6: R211.2, U62.4, U62.5
PRES0_CSB7: R255.2, R258.1, U202.4, U202.5
PRES0_CSB8: R261.2, R264.1, U73.4, U73.5
PRES1_CSB: R506.1, U507.3
PRES1_CSB1: R11.1, U4.3
PRES1_CSB2: R53.1, U16.3
PRES1_CSB3: R95.1, U28.3
PRES1_CSB4: R137.1, U40.3
PRES1_CSB5: R179.1, U52.3
PRES1_CSB6: R221.1, U64.3
RASPI_GPIO1: DS5.2, J3.1, TP1.TP
RASPI_GPIO2: DS6.2, J3.3, TP2.TP
RASPI_GPIO3: DS11.2, J11.1, TP34.TP
RASPI_GPIO4: DS12.2, J11.3, TP35.TP
RASPI_GPIO5: DS17.2, J19.1, TP67.TP
RASPI_GPIO6: DS18.2, J19.3, TP68.TP
RASPI_GPIO7: DS23.2, J27.1, TP100.TP
RASPI_GPIO8: DS24.2, J27.3, TP101.TP
RASPI_GPIO9: DS29.2, J35.1, TP133.TP
RASPI_GPIO10: DS30.2, J35.3, TP134.TP
RASPI_GPIO11: DS35.2, J43.1, TP166.TP
RASPI_GPIO12: DS36.2, J43.3, TP167.TP
RASPI_GPIO20: DS601.2, J604.1, TP605.TP
RASPI_GPIO26: DS602.2, J604.3, TP606.TP
RASPI_RESET_N: C601.1, J604.6, R312.2, TP611.TP
RASPI_RESET_N1: C14.1, J3.6, R22.2, TP4.TP
RASPI_RESET_N2: C39.1, J11.6, R64.2, TP37.TP
RASPI_RESET_N3: C64.1, J19.6, R106.2, TP70.TP
RASPI_RESET_N4: C89.1, J27.6, R148.2, TP103.TP
RASPI_RESET_N5: C114.1, J35.6, R190.2, TP136.TP
RASPI_RESET_N6: C139.1, J43.6, R232.2, TP169.TP
RESET_BITE_N: Q301.6, R311.1, R312.1, S301.3, S301.4, U302.7
RESET_BITE_N1: Q2.6, R15.1, R22.1, S1.3, S1.4, U6.7
RESET_BITE_N2: Q4.6, R57.1, R64.1, S2.3, S2.4, U18.7
RESET_BITE_N3: Q6.6, R99.1, R106.1, S3.3, S3.4, U30.7
RESET_BITE_N4: Q8.6, R141.1, R148.1, S4.3, S4.4, U42.7
RESET_BITE_N5: Q10.6, R183.1, R190.1, S5.3, S5.4, U54.7
RESET_BITE_N6: Q12.6, R225.1, R232.1, S6.3, S6.4, U66.7
TEMP0_A0: R256.2, R257.1, U201.1
TEMP0_A1: R262.2, R263.1, U74.1
TEMP0_I2C_A0: R502.2, U501.7
TEMP0_I2C_A1: R2.2, U11.7
TEMP0_I2C_A2: R44.2, U23.7
TEMP0_I2C_A3: R86.2, U35.7
TEMP0_I2C_A4: R128.2, U47.7
TEMP0_I2C_A5: R170.2, U59.7
TEMP0_I2C_A6: R212.2, U71.7
TEMP0_OS: TP506.TP, U501.3
TEMP0_OS1: TP26.TP, U11.3
TEMP0_OS2: TP59.TP, U23.3
TEMP0_OS3: TP92.TP, U35.3
TEMP0_OS4: TP125.TP, U47.3
TEMP0_OS5: TP158.TP, U59.3
TEMP0_OS6: TP191.TP, U71.3
TEMP0_OS7: TP203.TP, U201.5
TEMP0_OS8: TP199.TP, U74.5
TEMP1_I2C_A0: R501.2, U502.7
TEMP1_I2C_A1: R10.2, U12.7
TEMP1_I2C_A2: R52.2, U24.7
TEMP1_I2C_A3: R94.2, U36.7
TEMP1_I2C_A4: R136.2, U48.7
TEMP1_I2C_A5: R178.2, U60.7
TEMP1_I2C_A6: R220.2, U72.7
TEMP1_OS: TP507.TP, U502.3
TEMP1_OS1: TP27.TP, U12.3
TEMP1_OS2: TP60.TP, U24.3
TEMP1_OS3: TP93.TP, U36.3
TEMP1_OS4: TP126.TP, U48.3
TEMP1_OS5: TP159.TP, U60.3
TEMP1_OS6: TP192.TP, U72.3
TEMP_1WIRE_BI: J603.2, R605.1, R613.1
TEMP_1WIRE_BI1: J2.2, R7.1, R32.1
TEMP_1WIRE_BI2: J10.2, R49.1, R74.1
TEMP_1WIRE_BI3: J18.2, R91.1, R116.1
TEMP_1WIRE_BI4: J26.2, R133.1, R158.1
TEMP_1WIRE_BI5: J34.2, R175.1, R200.1
TEMP_1WIRE_BI6: J42.2, R217.1, R242.1
TEMP_1WIRE_BI_R: J601.7, R605.2
TEMP_1WIRE_BI_R1: J6.7, R32.2
TEMP_1WIRE_BI_R2: J14.7, R74.2
TEMP_1WIRE_BI_R3: J22.7, R116.2
TEMP_1WIRE_BI_R4: J30.7, R158.2
TEMP_1WIRE_BI_R5: J38.7, R200.2
TEMP_1WIRE_BI_R6: J46.7, R242.2
UART_RASPI_RXD_MCU_TXD: J602.1, R610.2
UART_RASPI_RXD_MCU_TXD1: J8.1, R34.2
UART_RASPI_RXD_MCU_TXD2: J16.1, R76.2
UART_RASPI_RXD_MCU_TXD3: J24.1, R118.2
UART_RASPI_RXD_MCU_TXD4: J32.1, R160.2
UART_RASPI_RXD_MCU_TXD5: J40.1, R202.2
UART_RASPI_RXD_MCU_TXD6: J48.1, R244.2
UART_RASPI_RXD_MCU_TXD_R: J601.10, R610.1
UART_RASPI_RXD_MCU_TXD_R1: J6.10, R34.1
UART_RASPI_RXD_MCU_TXD_R2: J14.10, R76.1
UART_RASPI_RXD_MCU_TXD_R3: J22.10, R118.1
UART_RASPI_RXD_MCU_TXD_R4: J30.10, R160.1
UART_RASPI_RXD_MCU_TXD_R5: J38.10, R202.1
UART_RASPI_RXD_MCU_TXD_R6: J46.10, R244.1
UART_RASPI_TXD_MCU_RXD: J602.3, R609.2
UART_RASPI_TXD_MCU_RXD1: J8.3, R33.2
UART_RASPI_TXD_MCU_RXD2: J16.3, R75.2
UART_RASPI_TXD_MCU_RXD3: J24.3, R117.2
UART_RASPI_TXD_MCU_RXD4: J32.3, R159.2
UART_RASPI_TXD_MCU_RXD5: J40.3, R201.2
UART_RASPI_TXD_MCU_RXD6: J48.3, R243.2
UART_RASPI_TXD_MCU_RXD_R: J601.8, R609.1
UART_RASPI_TXD_MCU_RXD_R1: J6.8, R33.1
UART_RASPI_TXD_MCU_RXD_R2: J14.8, R75.1
UART_RASPI_TXD_MCU_RXD_R3: J22.8, R117.1
UART_RASPI_TXD_MCU_RXD_R4: J30.8, R159.1
UART_RASPI_TXD_MCU_RXD_R5: J38.8, R201.1
UART_RASPI_TXD_MCU_RXD_R6: J46.8, R243.1
USB_SHD: J302.S1, J302.S2, J302.S3, J302.S4, J302.S5, J302.S6, R301.2
USB_SHD1: J4.S1, J4.S2, J4.S3, J4.S4, J4.S5, J4.S6, R23.2
USB_SHD2: J12.S1, J12.S2, J12.S3, J12.S4, J12.S5, J12.S6, R65.2
USB_SHD3: J20.S1, J20.S2, J20.S3, J20.S4, J20.S5, J20.S6, R107.2
USB_SHD4: J28.S1, J28.S2, J28.S3, J28.S4, J28.S5, J28.S6, R149.2
USB_SHD5: J36.S1, J36.S2, J36.S3, J36.S4, J36.S5, J36.S6, R191.2
USB_SHD6: J44.S1, J44.S2, J44.S3, J44.S4, J44.S5, J44.S6, R233.2
VBAT: C401.1, J401.1, J402.2, U301.3
VBAT1: C20.1, J1.1, J7.2, U9.3
VBAT2: C45.1, J9.1, J15.2, U21.3
VBAT3: C70.1, J17.1, J23.2, U33.3
VBAT4: C95.1, J25.1, J31.2, U45.3
VBAT5: C120.1, J33.1, J39.2, U57.3
VBAT6: C145.1, J41.1, J47.2, U69.3
VBAT_J: J402.1, R402.2A, TP401.1
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
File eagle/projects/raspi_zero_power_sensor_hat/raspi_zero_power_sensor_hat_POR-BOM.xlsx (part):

Qty | 5x_Qty | Value | Device | Package | Parts | Description | ACCURACY | ACTUATOR_HEIGHT | ACUTATOR_ORIENTATION | CIRCUIT | CLIPPING | COLOR | CONTACTS | CONTACT_RATING | CONTINUOUS_DRAIN_CURRENT | CURRENT_DC | CURRENT_RATING | CURRENT_SAT | DATASHEET | DCR_MAX | DC_COLD_RESISTANCE | DIAMETER | DRILL | FET_TYPE | FINISH | FORWARD_CURRENT | FORWARD_VOLTAGE | FUNCTION | HEIGHT_BOTTOM | HEIGHT_TOP | INSULATED | INTERFACE | LOCKING | MANUFACTURER | MANUFACTURER_PN | MAX_CURRENT | MOUNTING_TYPE | MOUNT_ANGLE | MOUNT_TYPE | OUTPUT_ACTIVE | OUTPUT_ACTIVE_TIME | OUTPUT_BITS | OUTPUT_TYPE | PITCH | PLATING | POSITIONS | POWER | POWER_MAX | PRESSURE_TYPE | RATED_CURRENT | RDS_ON_MAX | RESOLUTION | RESPONSE_TIME | ROWS | SHIELDED | SRF | STARTUP_DELAY | SWITCH_FUNCTION | TEMP_COEFF | TERMINALS | TIMEOUT | TOLERANCE | TP_SIGNAL_NAME | VALUE | VDS | VENDOR | VENDOR_PN | VGS_MAX | VOLTAGE | VOLTAGE_RATING | _EXTERNAL_ | VENDOR_PN | VGS_MAX | VOLTAGE | VOLTAGE_RATING | _EXTERNAL_
3 | 15 | SL 70066 2PIN HOUSING | BOM_LINE_ITEM_BLI2 | BLANK | BOM701, BOM704, BOM707 |  |  |  |  |  |  |  |  |  |  |  |  |  | HW/docs/projects/raspi_zero_power_sensor_hat/datasheets/connectors/uart_1wire_p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 |  |  |  |  |  |  |  |  |  |  |  |  |  |  | Molex | 50-57-9402 |  |  |  |  |  |  |  |  |  |  |  |  |  |  |  |  |  |  |  |  |  |  |  |  |  |  |  |  | SL 70066 2PIN HOUSING |  | Digi-key | WM2900-ND
13 | 65 | SL 70058 GOLD CRIMP | BOM_LINE_ITEM_BLI6 | BLANK | BOM702, BOM703, BOM705, BOM706, BOM708, BOM709, BOM712, BOM713, BOM714, BOM715,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 |  |  |  |  |  |  |  |  |  |  |  |  |  | HW/docs/projects/raspi_zero_power_sensor_hat/datasheets/connectors/uart_1wire_p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 |  |  |  |  |  |  |  |  |  |  |  |  |  |  | Molex | 16020087 |  |  |  |  |  |  |  |  |  |  |  |  |  |  |  |  |  |  |  |  |  |  |  |  |  |  |  |  | SL 70058 GOLD CRIMP |  | Digi-key | WM2512CT-ND
1 | 5 | HEADER-RECT-MALE-2X5 | BOM_LINE_ITEM_BLI10 | BLANK | BOM710 |  |  |  |  |  |  |  |  |  |  |  |  |  | HW/docs/projects/raspi_zero_power_sensor_hat/datasheets/connectors/raspi_header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 |  |  |  |  |  |  |  |  |  |  |  |  |  |  | Harwin | M20-9980545 |  |  |  |  |  |  |  |  |  |  |  |  |  |  |  |  |  |  |  |  |  |  |  |  |  |  |  |  | HEADER-RECT-MALE-2X5 |  | Digi-key | 952-2380-ND
1 | 5 | SL 70066 4PIN HOUSING | BOM_LINE_ITEM_BLI4 | BLANK | BOM711 |  |  |  |  |  |  |  |  |  |  |  |  |  | HW/docs/projects/raspi_zero_power_sensor_hat/datasheets/connectors/uart_1wire_p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 |  |  |  |  |  |  |  |  |  |  |  |  |  |  | Molex | 50579404 |  |  |  |  |  |  |  |  |  |  |  |  |  |  |  |  |  |  |  |  |  |  |  |  |  |  |  |  | SL 70066 4PIN HOUSING |  | Digi-key | WM2902-ND
1 | 5 | SL 70066 3PIN HOUSING | BOM_LINE_ITEM_BLI3 | BLANK | BOM716 |  |  |  |  |  |  |  |  |  |  |  |  |  | HW/docs/projects/raspi_zero_power_sensor_hat/datasheets/connectors/uart_1wire_p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 |  |  |  |  |  |  |  |  |  |  |  |  |  |  | Molex | 50-57-9403 |  |  |  |  |  |  |  |  |  |  |  |  |  |  |  |  |  |  |  |  |  |  |  |  |  |  |  |  | SL 70066 3PIN HOUSING |  | Digi-key | WM2901-ND
2 | 10 | 1-Wire Temperature Sensor | BOM_LINE_ITEM_BLI7 | BLANK | BOM720, BOM721 |  |  |  |  |  |  |  |  |  |  |  |  |  | HW/docs/projects/raspi_zero_power_sensor_hat/datasheets/sensors/DS18B20.pdf |  |  |  |  |  |  |  |  |  |  |  |  |  |  | Maxim | DS18B20+ |  |  |  |  |  |  |  |  |  |  |  |  |  |  |  |  |  |  |  |  |  |  |  |  |  |  |  |  | 1-Wire Temperature Sensor |  | Digi-key | DS18B20+-ND
1 | 5 | HEADER-RECT-MALE-2X3 | BOM_LINE_ITEM_BLI1 | BLANK | BOM722 |  |  |  |  |  |  |  |  |  |  |  |  |  | HW/docs/projects/raspi_zero_power_sensor_hat/datasheets/connectors/raspi_header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 |  |  |  |  |  |  |  |  |  |  |  |  |  |  | Harwin | M20-9980345 |  |  |  |  |  |  |  |  |  |  |  |  |  |  |  |  |  |  |  |  |  |  |  |  |  |  |  |  | HEADER-RECT-MALE-2X3 |  | Digi-key | 952-2120-ND
5 | 25 | 10uF | CAP_10UF0_0805_0805 | C0805 | C301, C401, C406, C407, C408 | Chip Capacitor |  |  |  |  |  |  |  |  |  |  |  |  | HW/docs/projects/raspi_zero_power_sensor_hat/datasheets/passives/c02e.pdf |  |  |  |  |  |  |  |  |  |  |  |  |  |  | Murata | GRM21BR61C106KE15L |  |  |  |  |  |  |  |  |  |  |  |  |  |  |  |  |  |  |  |  |  |  |  | X5R |  |  | 0.1 |  | 10uF |  | Digi-key | 490-3886-1-ND |  | 16V
12 | 60 | 100nF | CAP_100NF0_0603 | C0603 | C302, C501, C502, C506, C507, C508, C510, C511, C512, C513, C601, C602 | Chip Capacitor |  |  |  |  |  |  |  |  |  |  |  |  | HW/docs/projects/raspi_zero_power_sensor_hat/datasheets/passives/c02e.pdf |  |  |  |  |  |  |  |  |  |  |  |  |  |  | Murata | GRM188R71C104KA01D |  |  |  |  |  |  |  |  |  |  |  |  |  |  |  |  |  |  |  |  |  |  |  | X7R |  |  | 0.1 |  | 100nF |  | Digi-key | 490-1532-1-ND |  | 16V
1 | 5 | 22uF | CAP_22UF0_0805 | C0805 | C403 | Chip Capacitor |  |  |  |  |  |  |  |  |  |  |  |  | HW/docs/projects/raspi_zero_power_sensor_hat/datasheets/passives/c02e.pdf |  |  |  |  |  |  |  |  |  |  |  |  |  |  | Murata | GRM21BR61A226ME51L |  |  |  |  |  |  |  |  |  |  |  |  |  |  |  |  |  |  |  |  |  |  |  | X5R |  |  | 0.2 |  | 22uF |  | Digi-key | 490-10511-1-ND |  | 10V
1 | 5 | 18nF | CAP_18NF0_0603 | C0603 | C405 | Chip Capacitor |  |  |  |  |  |  |  |  |  |  |  |  | HW/docs/projects/raspi_zero_power_sensor_hat/datasheets/passives/c02e.pdf |  |  |  |  |  |  |  |  |  |  |  |  |  |  | Murata | GRM188R71H183JA01D |  |  |  |  |  |  |  |  |  |  |  |  |  |  |  |  |  |  |  |  |  |  |  | X7R |  |  | 0.05 |  | 18nF |  | Digi-key | 490-12544-1-ND |  | 50V
1 | 5 | 10nF | CAP_10NF0_0603 | C0603 | C505 | Chip Capacitor |  |  |  |  |  |  |  |  |  |  |  |  | HW/docs/projects/raspi_zero_power_sensor_hat/datasheets/passives/c02e.pdf |  |  |  |  |  |  |  |  |  |  |  |  |  |  | Murate | GRM188R71H103JA01D |  |  |  |  |  |  |  |  |  |  |  |  |  |  |  |  |  |  |  |  |  |  |  | X7R |  |  | 0.05 |  | 10nF |  | Digi-key | 490-9734-1-ND |  | 50V
1 | 5 | 10uF | CAP_10UF0_0603 | C0603 | C509 | Chip Capacitor |  |  |  |  |  |  |  |  |  |  |  |  | HW/docs/projects/raspi_zero_power_sensor_hat/datasheets/passives/c02e.pdf |  |  |  |  |  |  |  |  |  |  |  |  |  |  | Murata | GRM188R61A106KE69D |  |  |  |  |  |  |  |  |  |  |  |  |  |  |  |  |  |  |  |  |  |  |  | X5R |  |  | 0.1 |  | 10uF |  | Digi-key | 490-10474-1-ND |  | 10V
4 | 20 | YELLOW | LED_Y2V0WURTH_0603 | LED0603 | DS301, DS402, DS601, DS602 | Chip LED |  |  |  |  |  |  |  |  |  |  |  |  | HW/docs/projects/raspi_zero_power_sensor_hat/datasheets/charger/150060YS75000.p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 |  |  |  |  |  |  | 20mA | 2.0V |  |  |  |  |  |  | Wurth | 150060YS75000 |  |  |  |  |  |  |  |  |  |  |  |  |  |  |  |  |  |  |  |  |  |  |  |  |  |  |  |  | YELLOW |  | Digi-key | 732-4981-1-ND
1 | 5 | GREEN | LED_G3V2WURTH_0603 | LED0603 | DS302 | Chip LED |  |  |  |  |  |  |  |  |  |  |  |  | HW/docs/projects/raspi_zero_power_sensor_hat/datasheets/charger/150060GS75000.p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 |  |  |  |  |  |  | 20mA | 3.2V |  |  |  |  |  |  | Wurth | 150060GS75000 |  |  |  |  |  |  |  |  |  |  |  |  |  |  |  |  |  |  |  |  |  |  |  |  |  |  |  |  | GREEN |  | Digi-key | 732-4971-1-ND
1 | 5 | BLUE | LED_B3V2WURTH_0603 | LED0603 | DS401 | Chip LED |  |  |  |  |  |  |  |  |  |  |  |  | HW/docs/projects/raspi_zero_power_sensor_hat/datasheets/charger/150060BS75000.p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 |  |  |  |  |  |  | 20mA | 3.2V |  |  |  |  |  |  | Wurth | 150060BS75000 |  |  |  |  |  |  |  |  |  |  |  |  |  |  |  |  |  |  |  |  |  |  |  |  |  |  |  |  | BLUE |  | Digi-key | 732-4966-1-ND
1 | 5 | FUSE-50MA | FUSE_CHIP_0603 | R0603 | F601 | FUSE |  |  |  |  |  |  |  |  |  |  | 50mA |  | HW/docs/projects/raspi_zero_power_sensor_hat/datasheets/passives/AccuGuardLC_06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 |  | 3.4OHM |  |  |  |  |  |  |  |  |  |  |  |  | AVX | F0603G0R05FNTR |  |  |  |  |  |  |  |  |  |  |  |  |  |  |  |  |  | FAST |  |  |  |  |  |  |  |  |  |  | FUSE-50MA |  | Digi-key | 478-6871-1-ND |  |  | 32Vdc
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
